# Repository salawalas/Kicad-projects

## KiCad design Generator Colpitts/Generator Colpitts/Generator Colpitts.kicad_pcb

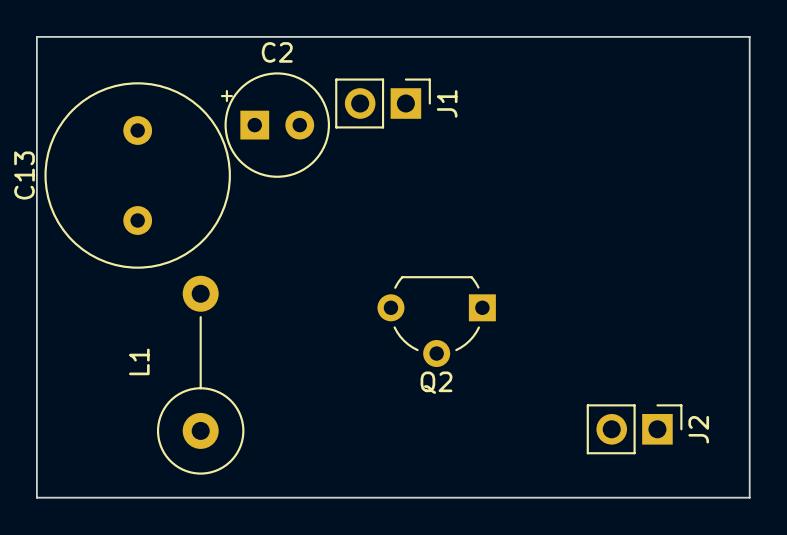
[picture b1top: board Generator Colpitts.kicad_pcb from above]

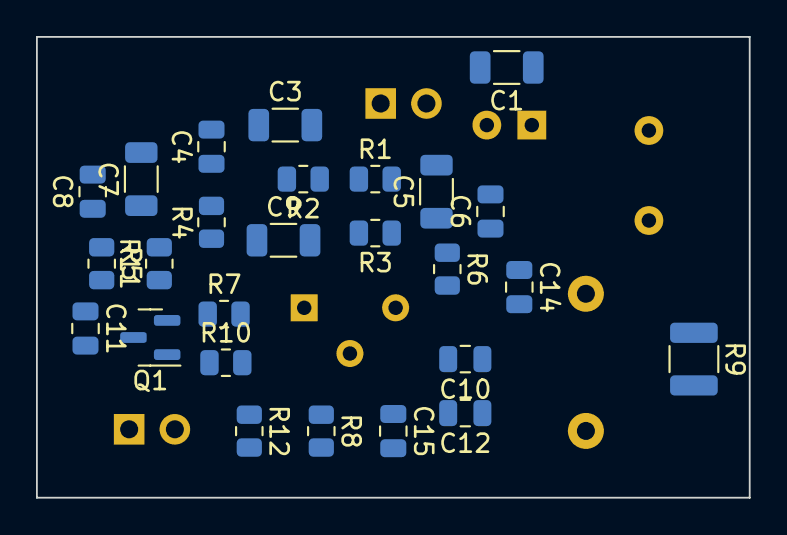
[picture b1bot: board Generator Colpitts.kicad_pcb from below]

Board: 2 copper layers, 39.6 x 25.6 mm, 32 parts (26 on the bottom side), 13 nets, no tracks yet.

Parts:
C1, C5: 100n; C_1206_3216Metric
C2: 47u/16V; CP_Radial_Tantal_D5.5mm_P2.50mm
C3, C7, C9: 47n; C_1206_3216Metric
C4, C6: 1n; C_0805_2012Metric
C8: 2n2; C_0805_2012Metric
C10: 5.6p; C_0805_2012Metric
C11: 47n; C_0805_2012Metric
C12: 24p; C_0805_2012Metric
C13: 3-12pF; C_Radial_D10.0mm_H12.5mm_P5.00mm
C14: 33p; C_0805_2012Metric
C15: 16p; C_0805_2012Metric
J1, J2: Conn_01x02_Female; PinHeader_1x02_P2.54mm_Vertical
L1: 48nH; L_Axial_L14.0mm_D4.5mm_P7.62mm_Vertical_Fastron_LACC
Q1: BFS17; SOT-23
Q2: BF240; TO-92L_Wide
R1: 100; R_0805_2012Metric
R2, R7: 51; R_0805_2012Metric
R3: 1k3; R_0805_2012Metric
R4: 4k7; R_0805_2012Metric
R5: 33; R_0805_2012Metric
R6: 8k2; R_0805_2012Metric
R8: 2k7; R_0805_2012Metric
R9: R_Small; R_1210_3225Metric
R10: 7k5; R_0805_2012Metric
R11: 300; R_0805_2012Metric
R12: 430; R_0805_2012Metric

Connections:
+12V: C1.1, C2.1, C5.1, C6.1, J1.1, R1.2, R2.1
GND: C1.2, C2.2, C3.2, C4.2, C5.2, C6.2, C7.2, C8.2, C13.2, C14.1, C15.2, J1.2, J2.2, L1.1, R8.2, R9.2, R10.1, R11.2, R12.2
unnamed: C3.1, C4.1, R1.1, R3.1, R6.1
unnamed: C7.1, C8.1, R2.2, R4.2, R5.1
unnamed: C9.1, R4.1, R7.2, R10.2
unnamed: C9.2, Q2.1 (C), R3.2
unnamed: C10.1, C13.1, C14.2, L1.2, R9.1
unnamed: C10.2, C12.1, Q2.3 (B), R6.2, R8.1
unnamed: C11.1, Q1.2 (E), R11.1
unnamed: C11.2, J2.1
unnamed: C12.2, C15.1, Q2.2 (E), R12.1
unnamed: Q1.1 (B), R7.1
unnamed: Q1.3 (C), R5.2

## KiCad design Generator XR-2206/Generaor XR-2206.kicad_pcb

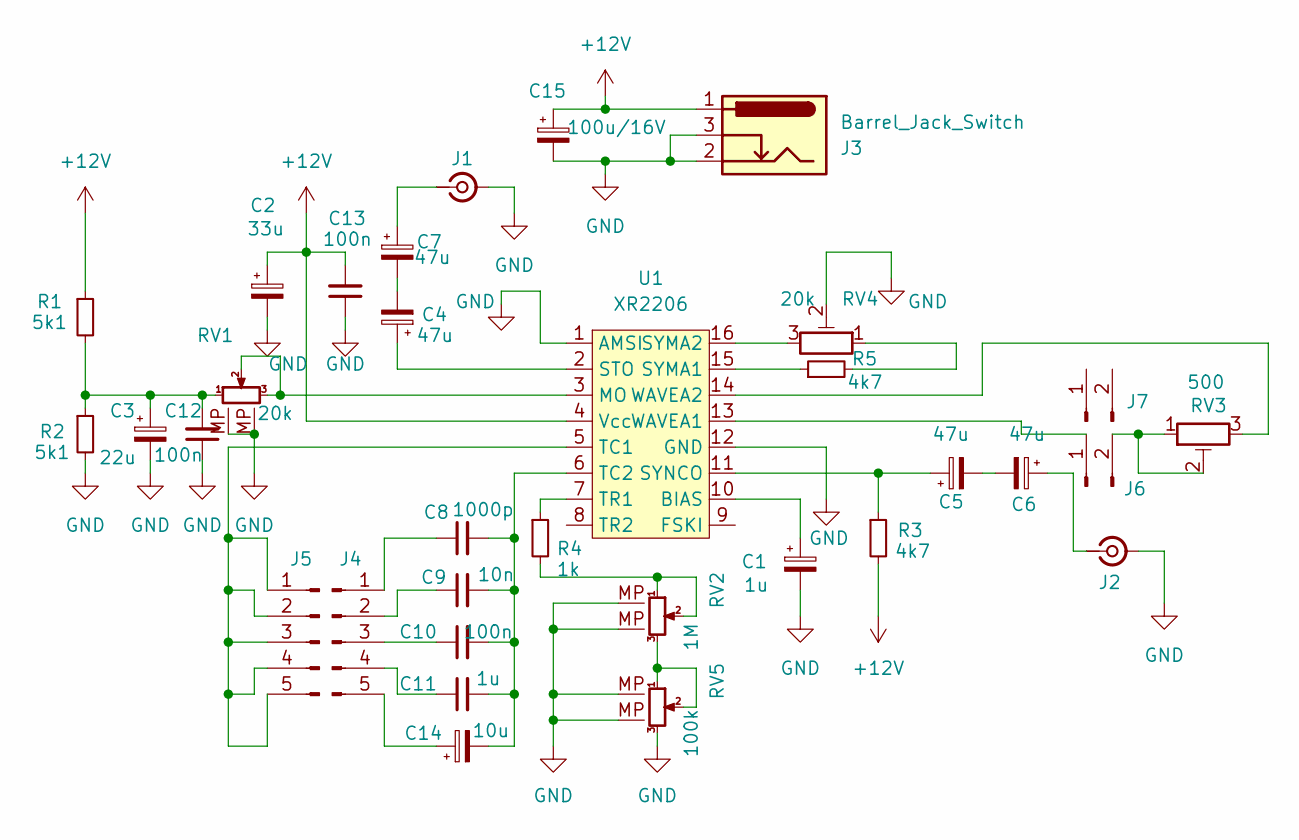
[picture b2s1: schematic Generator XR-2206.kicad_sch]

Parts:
C1: 1u; CP_Radial_Tantal_D5.5mm_P5.00mm
C2: 33u; CP_Radial_Tantal_D5.5mm_P5.00mm
C3: 22u; CP_Radial_Tantal_D5.5mm_P5.00mm
C4, C5, C6, C7: 47u; CP_Radial_D6.3mm_P2.50mm
C8: 1000p; C_Axial_L5.1mm_D3.1mm_P7.50mm_Horizontal
C9: 10n; C_Axial_L5.1mm_D3.1mm_P7.50mm_Horizontal
C10, C12, C13: 100n; C_Axial_L5.1mm_D3.1mm_P7.50mm_Horizontal
C11: 1u; C_Axial_L5.1mm_D3.1mm_P7.50mm_Horizontal
C14: 10u; CP_Radial_D6.3mm_P2.50mm
C15: 100u/16V; CP_Radial_D6.3mm_P2.50mm
J1, J2: Conn_Coaxial_Small; BNC_TEConnectivity_1478035_Horizontal
J3: Barrel_Jack_Switch; BarrelJack_GCT_DCJ200-10-A_Horizontal
J4, J5: Conn_01x05_Pin; PinHeader_1x05_P2.54mm_Vertical
J6, J7: Conn_01x02_Pin; PinHeader_1x02_P2.54mm_Vertical
R1, R2: 5k1; R_Axial_DIN0207_L6.3mm_D2.5mm_P10.16mm_Horizontal
R3, R5: 4k7; R_Axial_DIN0207_L6.3mm_D2.5mm_P10.16mm_Horizontal
R4: 1k; R_Axial_DIN0207_L6.3mm_D2.5mm_P10.16mm_Horizontal
RV1: 20k; Potentiometer_Alps_RK09K_Single_Vertical
RV2: 1M; Potentiometer_Alps_RK09K_Single_Vertical
RV3: 500; Potentiometer_Bourns_3296W_Vertical
RV4: 20k; Potentiometer_Bourns_3296W_Vertical
RV5: 100k; Potentiometer_Alps_RK09K_Single_Vertical
U1: XR2206; DIP-16_W7.62mm_Socket

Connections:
+12V: C2.1, C13.2, C15.1, J3.1, R1.1, R3.2, U1.4 (Vcc)
GND: C1.2, C2.2, C3.2, C12.1, C13.1, C15.2, J1.2 (Ext), J2.2 (Ext), J3.2, J3.3, R2.2, RV1.MP, RV2.MP, RV4.2, RV5.3, RV5.MP, U1.1 (AMSI), U1.12 (GND)
unnamed: C4.2, C7.2
unnamed: C5.2, C6.2
unnamed: C3.1, C12.2, R1.2, R2.1, RV1.1
unnamed: C7.1, J1.1 (In)
unnamed: C6.1, J2.1 (In)
unnamed: C8.1, J4.1
unnamed: C9.1, J4.2
unnamed: C10.1, J4.3
unnamed: C11.1, J4.4
unnamed: C14.1, J4.5
unnamed: J5.1, J5.2, J5.3, J5.4, J5.5, U1.5 (TC1)
unnamed: J6.1, U1.13 (WAVEA1)
unnamed: J6.2, RV3.1, RV3.2
unnamed: R4.2, RV2.1, RV2.2
unnamed: R5.2, RV4.1
unnamed: RV2.3, RV5.1, RV5.2
unnamed: C1.1, U1.10 (BIAS)
unnamed: RV1.2, RV1.3, U1.3 (MO)
unnamed: C4.1, U1.2 (STO)
unnamed: R5.1, U1.15 (SYMA1)
unnamed: RV4.3, U1.16 (SYMA2)
unnamed: C5.1, R3.1, U1.11 (SYNCO)
unnamed: C8.2, C9.2, C10.2, C11.2, C14.2, U1.6 (TC2)
unnamed: R4.1, U1.7 (TR1)
unnamed: RV3.3, U1.14 (WAVEA2)

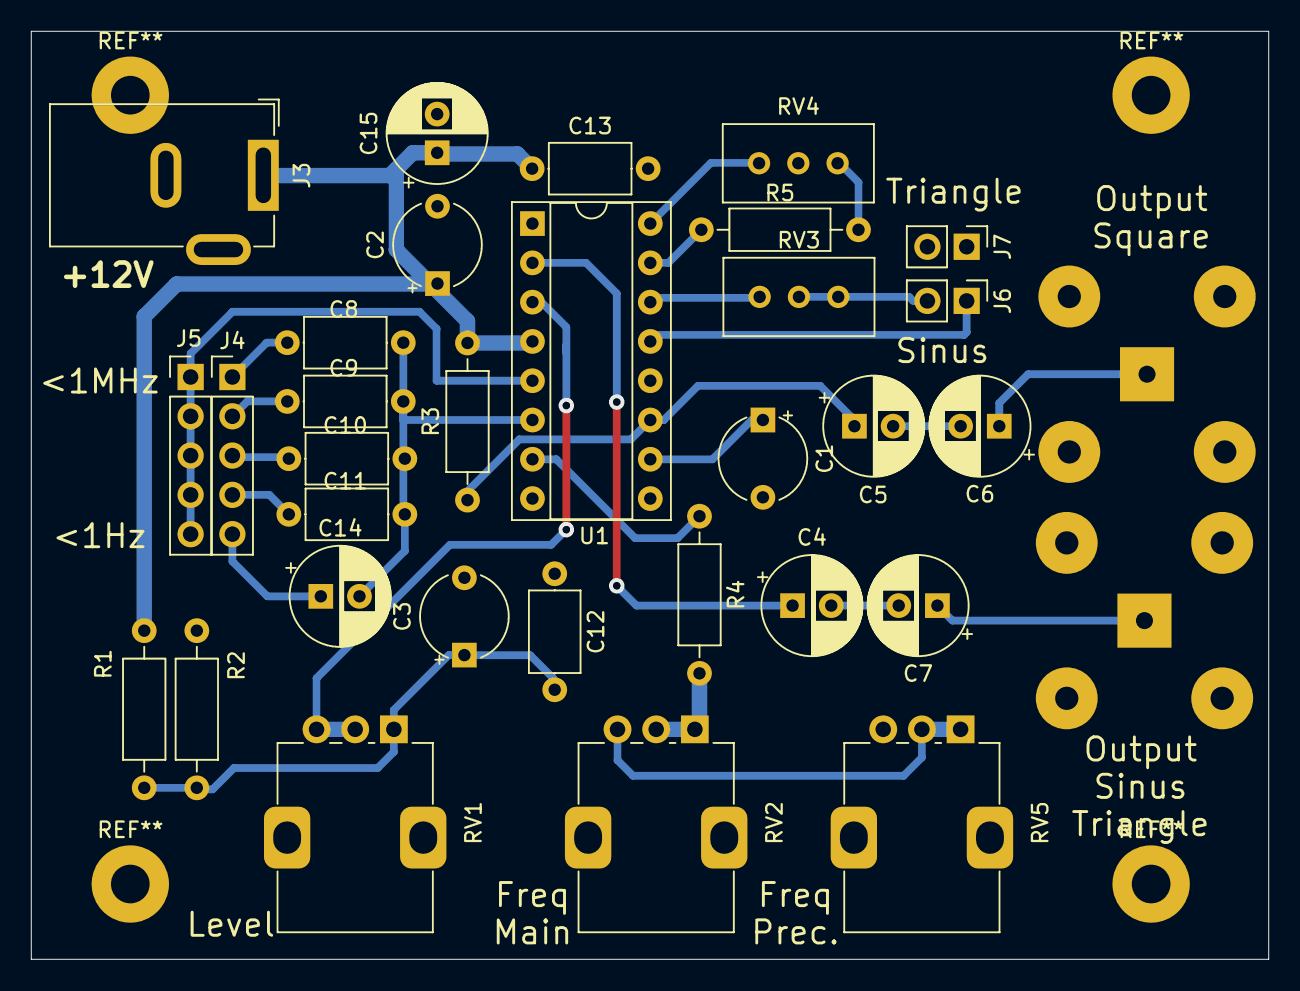
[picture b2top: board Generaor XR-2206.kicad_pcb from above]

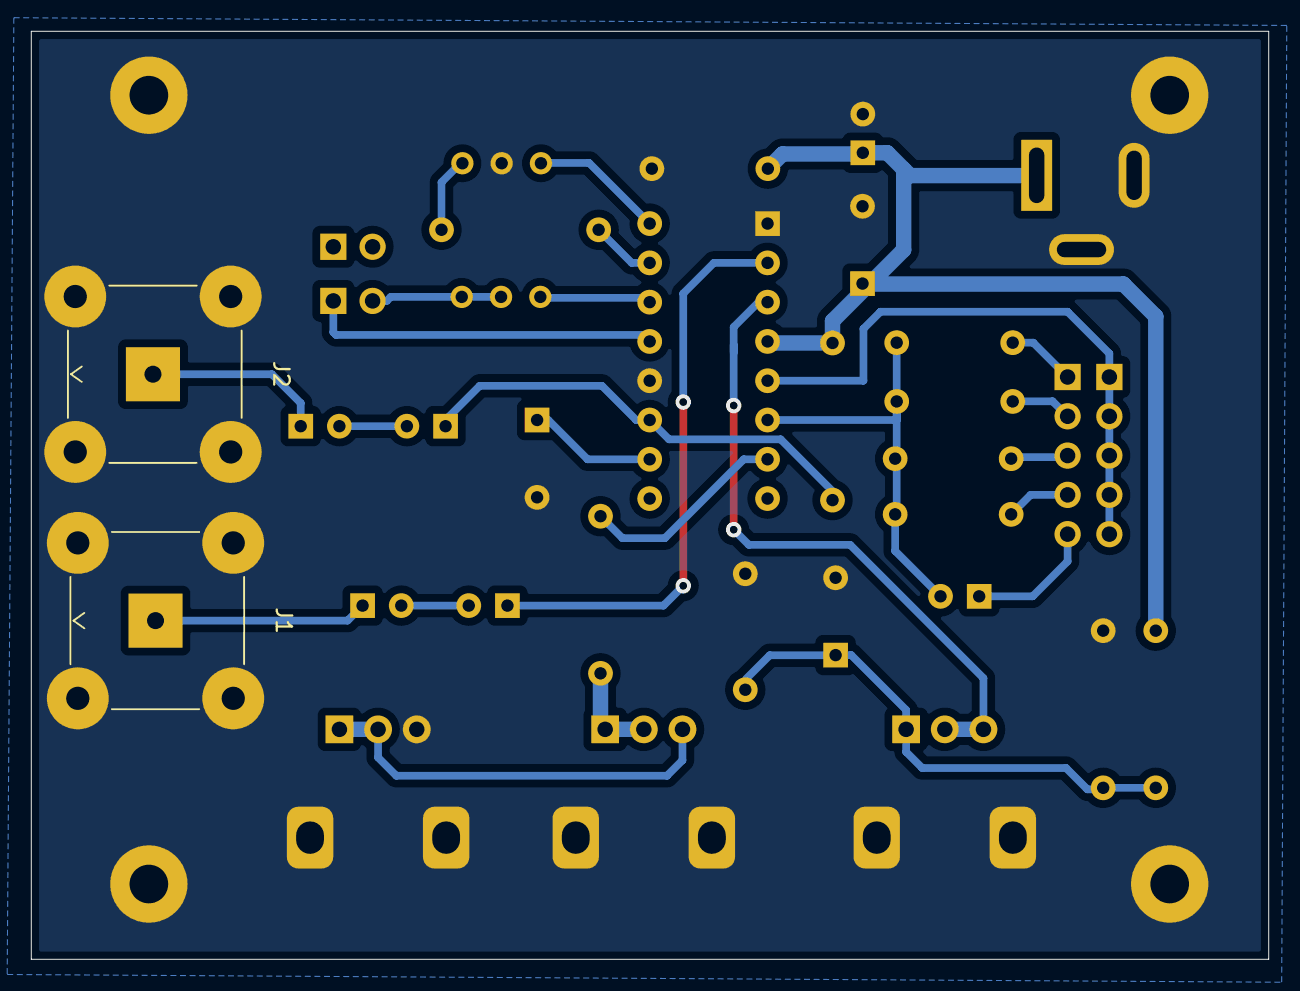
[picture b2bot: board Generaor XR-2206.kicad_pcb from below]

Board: 2 copper layers, 80.0 x 60.0 mm, 33 parts (2 on the bottom side), 27 nets.

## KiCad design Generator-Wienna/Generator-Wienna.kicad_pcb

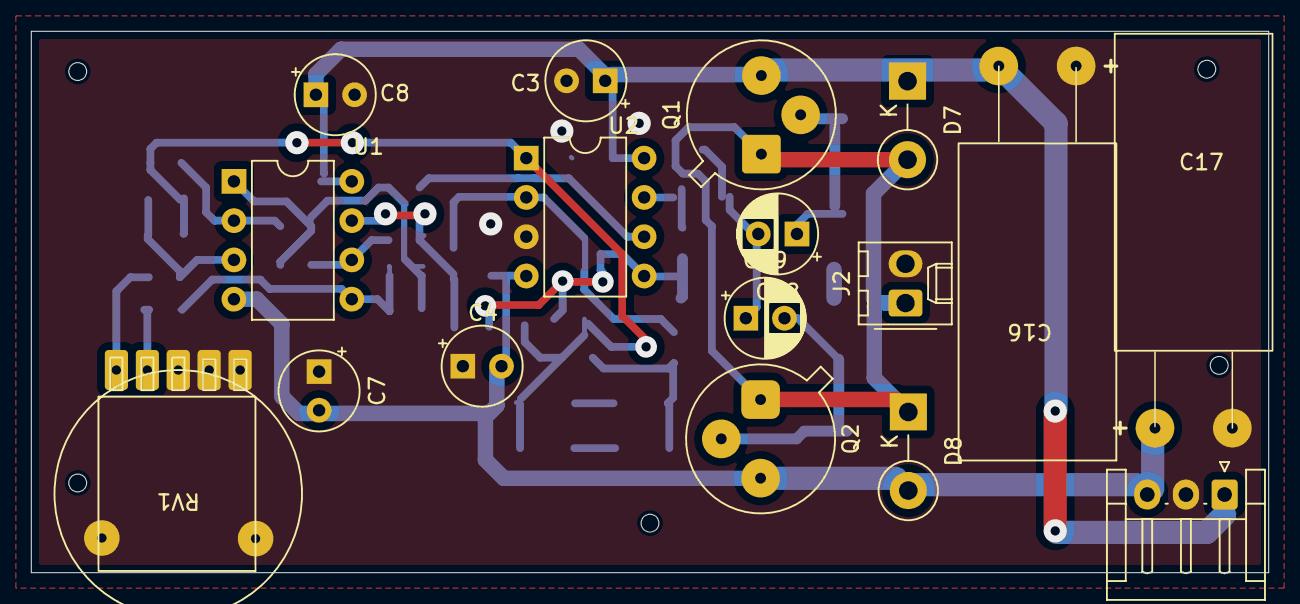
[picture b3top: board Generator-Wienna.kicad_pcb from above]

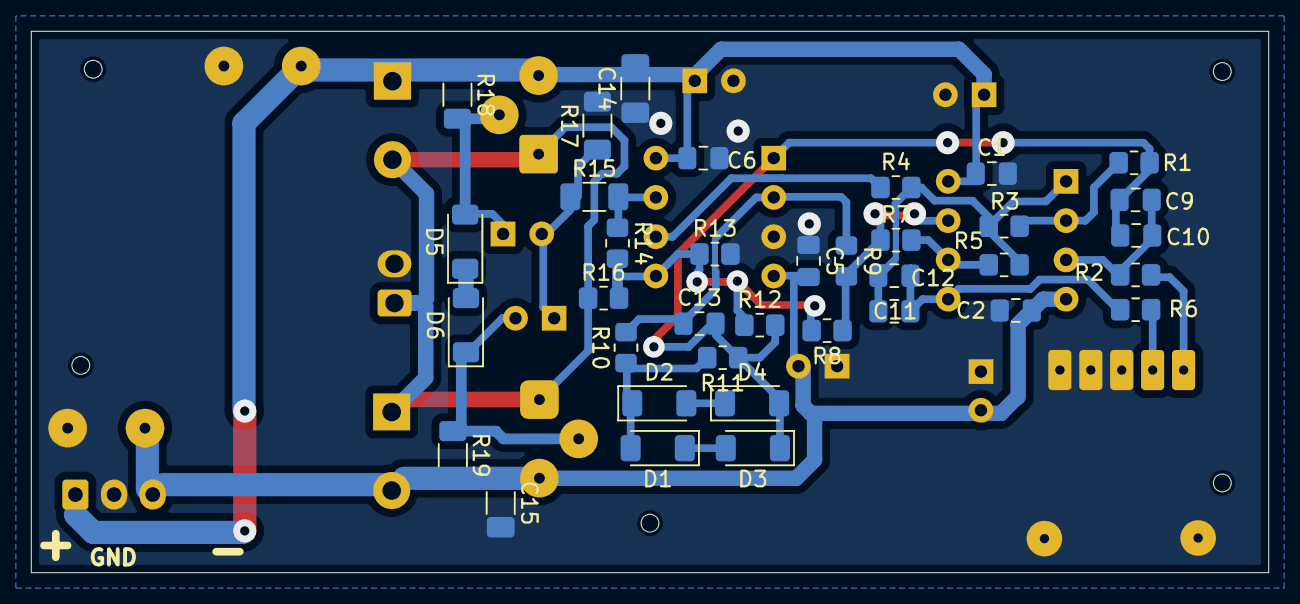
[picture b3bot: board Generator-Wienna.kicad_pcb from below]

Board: 2 copper layers, 80.0 x 35.0 mm, 53 parts (36 on the bottom side), 24 nets.

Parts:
C1, C2, C5, C6: 100n; C_0805_2012Metric_Pad1.18x1.45mm_HandSolder
C3, C4, C7, C8: 22u/10v; CP_Radial_Tantal_D5.0mm_P2.50mm
C9, C10, C11, C12: 220n; C_0805_2012Metric_Pad1.18x1.45mm_HandSolder
C13: 270p; C_0805_2012Metric_Pad1.18x1.45mm_HandSolder
C14, C15: 100n; C_1206_3216Metric_Pad1.33x1.80mm_HandSolder
C16: 2200u/6.3v; 2200u_6.3V
C17: 2200u/6.3V; 2200u_6.3V
C18, C19: 100u/16V; CP_Radial_D5.0mm_P2.50mm
D1, D2, D3, D4, D5, D6: 1N4148W; D_MiniMELF
D7, D8: 1N4001; D_DO-15_P5.08mm_Vertical_KathodeUp
J1: Power; JST_EH_S3B-EH_1x03_P2.50mm_Horizontal
J2: Output; Molex_KK-254_AE-6410-02A_1x02_P2.54mm_Vertical
Q1: BC141; TO-39-3
Q2: BC161; TO-39-3
R1, R3, R4, R5, R7, R8, R12, R14: 10k; R_0805_2012Metric_Pad1.20x1.40mm_HandSolder
R2, R6: 43k; R_0805_2012Metric_Pad1.20x1.40mm_HandSolder
R9: 4k7; R_0805_2012Metric_Pad1.20x1.40mm_HandSolder
R10: 1k8; R_0805_2012Metric_Pad1.20x1.40mm_HandSolder
R11: 3k9; R_0805_2012Metric_Pad1.20x1.40mm_HandSolder
R13: 15k; R_0805_2012Metric_Pad1.20x1.40mm_HandSolder
R15: 100; R_1206_3216Metric_Pad1.30x1.75mm_HandSolder
R16: 100k; R_0805_2012Metric_Pad1.20x1.40mm_HandSolder
R17: 5k1; R_1206_3216Metric_Pad1.30x1.75mm_HandSolder
R18, R19: 2k; R_1206_3216Metric_Pad1.30x1.75mm_HandSolder
RV1: Potencjometr_podwójny_mp3
U1, U2: RC4558; DIP-8_W7.62mm

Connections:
+5V: C1.1, C3.1, C6.1, C8.1, C14.2, C16.1, D7.1 (K), J1.1, Q1.3 (C), R18.1, U1.8 (V+), U2.8 (V+)
-5V: C2.1, C4.2, C5.2, C7.2, C15.1, C17.2, D8.2 (A), J1.3, Q2.3 (C), R19.2, U1.4 (V-), U2.4 (V-)
GND: C1.2, C2.2, C3.2, C4.1, C5.1, C6.2, C7.1, C8.2, C14.1, C15.2, C16.2, C17.1, J1.2, J2.2, R13.2, R17.2, RV1.1 (GND), RV1.2 (L_slider), RV1.3 (R_slider), RV1.6 (GND), RV1.7 (GND), U2.3 (+)
unnamed: C11.1, C12.1, R3.2, R4.2, R5.2, U1.1
unnamed: C18.2, C19.1, R15.1, R17.1
unnamed: D1.2 (A), D2.1 (K), R10.1, R11.2
unnamed: D1.1 (K), D3.2 (A)
unnamed: D2.2 (A), D4.1 (K)
unnamed: C9.1, C10.1, C13.2, D3.1 (K), D4.2 (A), R1.1, R11.1, R12.2, U2.1
unnamed: C18.1, D5.2 (A), Q1.2 (B), R18.2
unnamed: D5.1 (K), D6.2 (A)
unnamed: C19.2, D6.1 (K), Q2.2 (B), R19.1
unnamed: D7.2 (A), D8.1 (K), J2.1, Q1.1 (E), Q2.1 (E), R16.1
unnamed: R7.1, R8.1, R9.2, U1.7
unnamed: R14.1, R15.2, U2.7
unnamed: R2.1, RV1.5 (L_out)
unnamed: R6.1, RV1.4 (R_out)
unnamed: C9.2, C10.2, R2.2, U1.3 (+)
unnamed: R1.2, R3.1, U1.2 (-)
unnamed: C11.2, C12.2, R6.2, U1.5 (+)
unnamed: R5.1, R7.2, U1.6 (-)
unnamed: C13.1, R9.1, R10.2, U2.2 (-)
unnamed: R8.2, R12.1, R13.1, R14.2, R16.2, U2.5 (+)
unnamed: R4.1, U2.6 (-)

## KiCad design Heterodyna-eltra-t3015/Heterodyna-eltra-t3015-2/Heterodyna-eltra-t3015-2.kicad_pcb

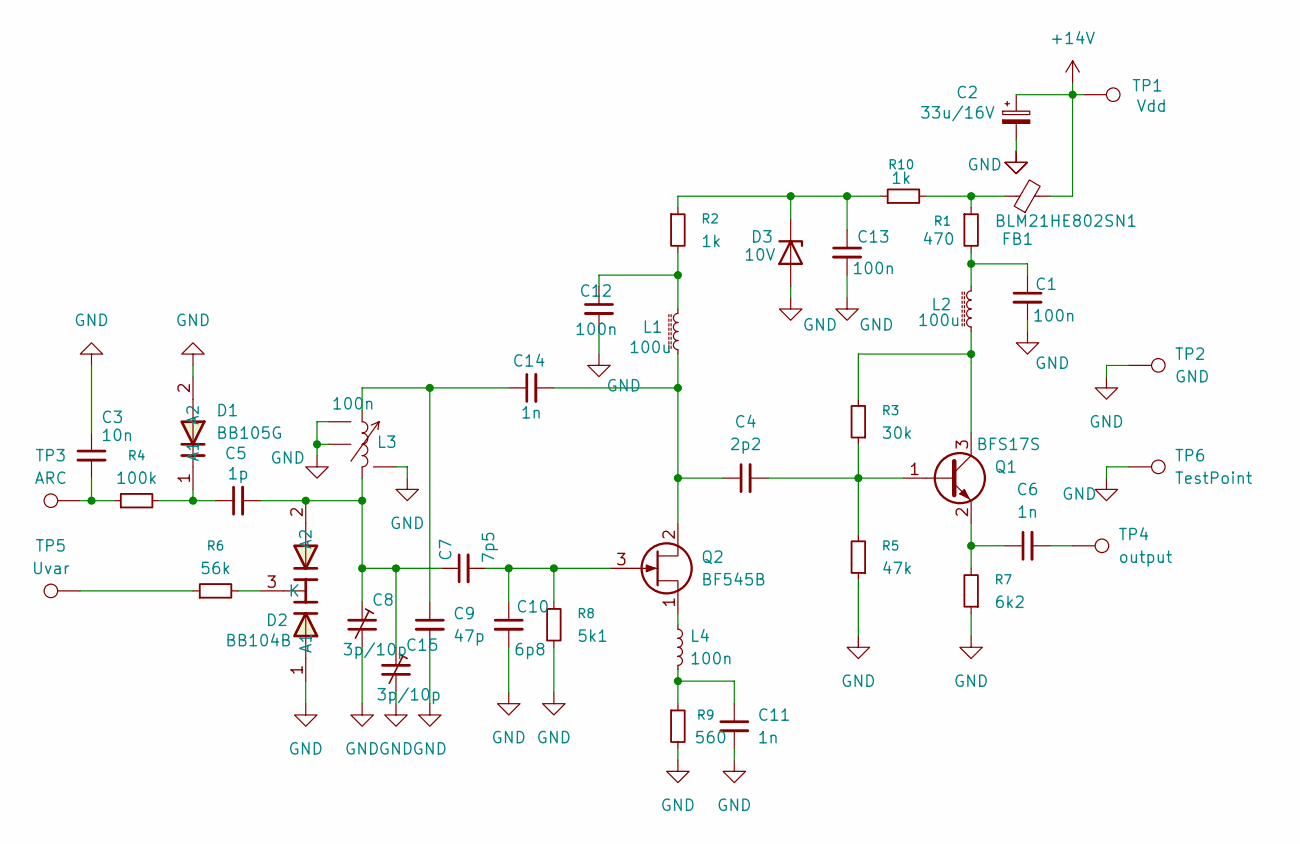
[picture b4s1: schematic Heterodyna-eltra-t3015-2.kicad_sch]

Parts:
C1, C12, C13: 100n; C_0805_2012Metric
C2: 33u/16V; CP_Radial_Tantal_D6.0mm_P2.50mm
C3: 10n; C_0805_2012Metric
C4: 2p2; C_0805_2012Metric
C5: 1p; C_0805_2012Metric
C6, C11, C14: 1n; C_0805_2012Metric
C7: 7p5; C_0805_2012Metric
C8: 3p/10p; Trymer 3-10pF
C9: 47p; C_0805_2012Metric
C10: 6p8; C_0805_2012Metric
C15: 3p/10p; Trymer 10pF
D1: BB105G
D2: BB104B
D3: 10V; D_DO-35_SOD27_P3.81mm_Vertical_AnodeUp
FB1: BLM21HE802SN1; L_0805_2012Metric
L1, L2: 100u; L_1206_3216Metric
L3: 100n; Cewka-powietrzna-5mm
L4: 100n; L_0805_2012Metric
Q1: BFS17S; TSOT-23
Q2: BF545B; SOT-23
R1: 470; R_1206_3216Metric
R2, R10: 1k; R_0805_2012Metric
R3: 30k; R_0805_2012Metric
R4: 100k; R_0805_2012Metric
R5: 47k; R_0805_2012Metric
R6: 56k; R_0805_2012Metric
R7: 6k2; R_0805_2012Metric
R8: 5k1; R_0805_2012Metric
R9: 560; R_0805_2012Metric
TP1: Vdd; SolderWire-0.1sqmm_1x01_D0.4mm_OD1mm
TP2: GND; SolderWire-0.1sqmm_1x01_D0.4mm_OD1mm
TP3: ARC; SolderWire-0.1sqmm_1x01_D0.4mm_OD1mm
TP4: output; SolderWire-0.1sqmm_1x01_D0.4mm_OD1mm
TP5: Uvar; SolderWire-0.1sqmm_1x01_D0.4mm_OD1mm
TP6: TestPoint; Pin_D0.7mm_L6.5mm_W1.8mm_FlatFork

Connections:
+14V: C2.1, FB1.2, TP1.1
GND: C1.2, C2.2, C3.1, C8.2, C9.2, C10.2, C11.2, C12.2, C13.2, C15.2, D1.2 (A2), D2.1 (A1), D3.2 (A), L3.4 (base), L3.5 (base), L3.6 (base), R5.1, R7.1, R8.2, R9.2, TP2.1, TP6.1
unnamed: C1.1, L2.2, R1.2
unnamed: C3.2, R4.1, TP3.1
unnamed: C6.2, TP4.1
unnamed: C11.1, L4.2, R9.1
unnamed: C12.1, L1.2, R2.2
unnamed: C9.1, C14.1, L3.1
unnamed: C5.1, D1.1 (A1), R4.2
unnamed: C5.2, C7.1, C8.1, C15.1, D2.2 (A2), L3.2
unnamed: D2.3 (K), R6.2
unnamed: C13.1, D3.1 (K), R2.1, R10.1
unnamed: FB1.1, R1.1, R10.2
unnamed: C4.2, Q1.1 (B), R3.1, R5.2
unnamed: L2.1, Q1.3 (C), R3.2
unnamed: C6.1, Q1.2 (E), R7.2
unnamed: C4.1, C14.2, L1.1, Q2.2 (D)
unnamed: C7.2, C10.1, Q2.3 (G), R8.1
unnamed: L4.1, Q2.1 (S)
unnamed: R6.1, TP5.1

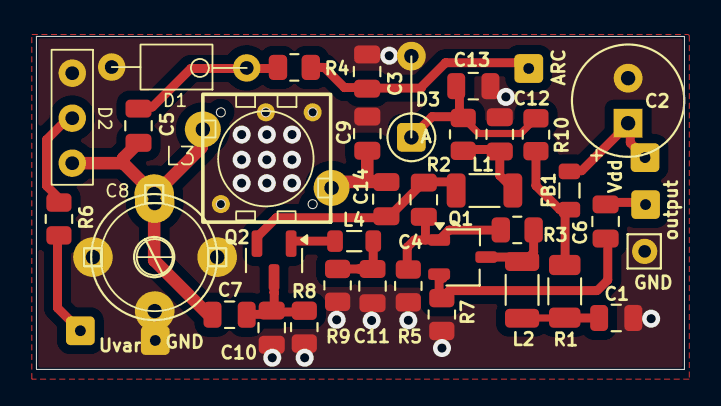
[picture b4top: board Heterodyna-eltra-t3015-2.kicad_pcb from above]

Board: 4 copper layers, 36.0 x 18.5 mm, 41 parts (0 on the bottom side), 20 nets.

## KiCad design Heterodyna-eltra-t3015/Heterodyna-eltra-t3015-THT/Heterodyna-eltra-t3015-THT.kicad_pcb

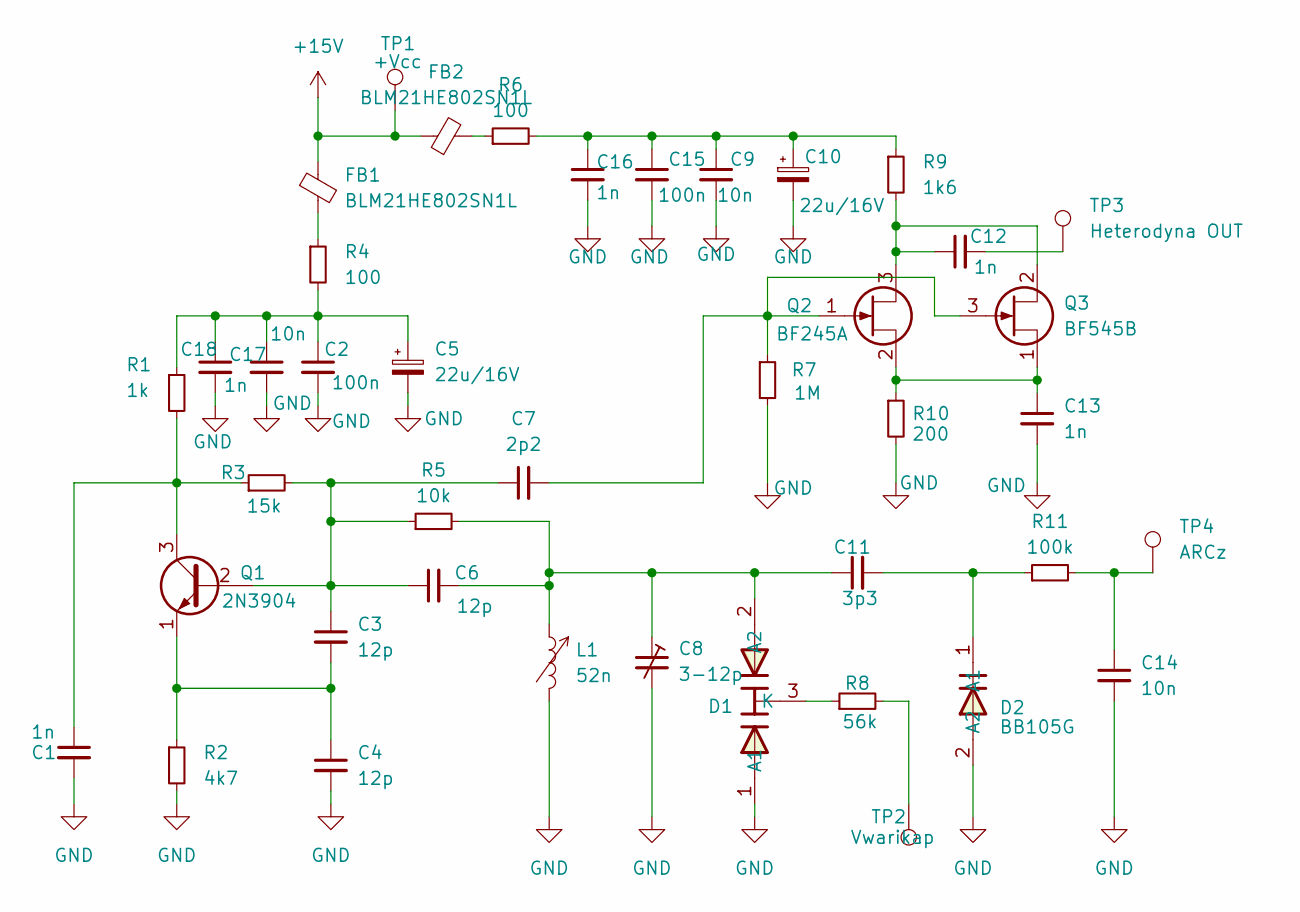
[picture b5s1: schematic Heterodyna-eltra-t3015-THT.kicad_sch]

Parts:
C1, C12, C13: 1n; C_Disc_D4.3mm_W1.9mm_P5.00mm
C2, C9: 100n; C_Disc_D4.7mm_W2.5mm_P5.00mm
C3, C4, C6: 12p; C_Disc_D4.3mm_W1.9mm_P5.00mm
C5, C10: 22u/16V; CP_Radial_Tantal_D5.0mm_P2.50mm
C7: 2p2; C_Disc_D4.3mm_W1.9mm_P5.00mm
C8: 3-12p; Trymer 3-10pF
C11: 3p3; C_Disc_D4.3mm_W1.9mm_P5.00mm
C14: 10n; C_Disc_D4.3mm_W1.9mm_P5.00mm
C15, C17: 10n; C_Disc_D4.7mm_W2.5mm_P5.00mm
C16, C18: 1n; C_Disc_D4.7mm_W2.5mm_P5.00mm
D1: BB104B
D2: BB105G
FB1, FB2: BLM21HE802SN1L; R_Axial_DIN0204_L3.6mm_D1.6mm_P7.62mm_Horizontal
L1: 52n; Cewka-powietrzna-5mm
Q1: 2N3904; TO-92_Wide
Q2: BF245A; TO-92_Wide
Q3: BF545B; SOT-23
R1: 1k; R_Axial_DIN0204_L3.6mm_D1.6mm_P7.62mm_Horizontal
R2: 4k7; R_Axial_DIN0204_L3.6mm_D1.6mm_P7.62mm_Horizontal
R3: 15k; R_Axial_DIN0204_L3.6mm_D1.6mm_P7.62mm_Horizontal
R4, R6: 100; R_Axial_DIN0204_L3.6mm_D1.6mm_P7.62mm_Horizontal
R5: 10k; R_Axial_DIN0204_L3.6mm_D1.6mm_P7.62mm_Horizontal
R7: 1M; R_Axial_DIN0204_L3.6mm_D1.6mm_P7.62mm_Horizontal
R8: 56k; R_Axial_DIN0204_L3.6mm_D1.6mm_P7.62mm_Horizontal
R9: 1k6; R_Axial_DIN0204_L3.6mm_D1.6mm_P7.62mm_Horizontal
R10: 200; R_Axial_DIN0204_L3.6mm_D1.6mm_P7.62mm_Horizontal
R11: 100k; R_Axial_DIN0204_L3.6mm_D1.6mm_P7.62mm_Horizontal
TP1: +Vcc; PinHeader_1x01_P1.00mm_Vertical
TP2: Vwarikap; PinHeader_1x01_P1.00mm_Vertical
TP3: Heterodyna OUT; PinHeader_1x01_P1.00mm_Vertical
TP4: ARCz; PinHeader_1x01_P1.00mm_Vertical

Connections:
+15V: FB1.2, FB2.1, TP1.1
GND: C1.2, C2.2, C4.2, C5.2, C8.2, C9.2, C10.2, C13.2, C14.2, C15.2, C16.2, C17.2, C18.2, D1.1 (A1), D2.2 (A2), L1.2, L1.4, L1.5, L1.6, L1.7, R2.2, R7.2, R10.2
unnamed: C9.1, C10.1, C15.1, C16.1, R6.2, R9.1
unnamed: C12.2, TP3.1
unnamed: C14.1, R11.2, TP4.1
unnamed: C2.1, C5.1, C17.1, C18.1, R1.1, R4.2
unnamed: C6.2, C8.1, C11.1, D1.2 (A2), L1.1, L1.3, R5.2
unnamed: D1.3 (K), R8.1
unnamed: C11.2, D2.1 (A1), R11.1
unnamed: FB1.1, R4.1
unnamed: FB2.2, R6.1
unnamed: C3.1, C6.1, C7.1, Q1.2 (B), R3.2, R5.1
unnamed: C1.1, Q1.3 (C), R1.2, R3.1
unnamed: C3.2, C4.1, Q1.1 (E), R2.1
unnamed: C12.1, Q2.3 (D), Q3.2 (D), R9.2
unnamed: C7.2, Q2.1 (G), Q3.3 (G), R7.1
unnamed: C13.1, Q2.2 (S), Q3.1 (S), R10.1
unnamed: R8.2, TP2.1

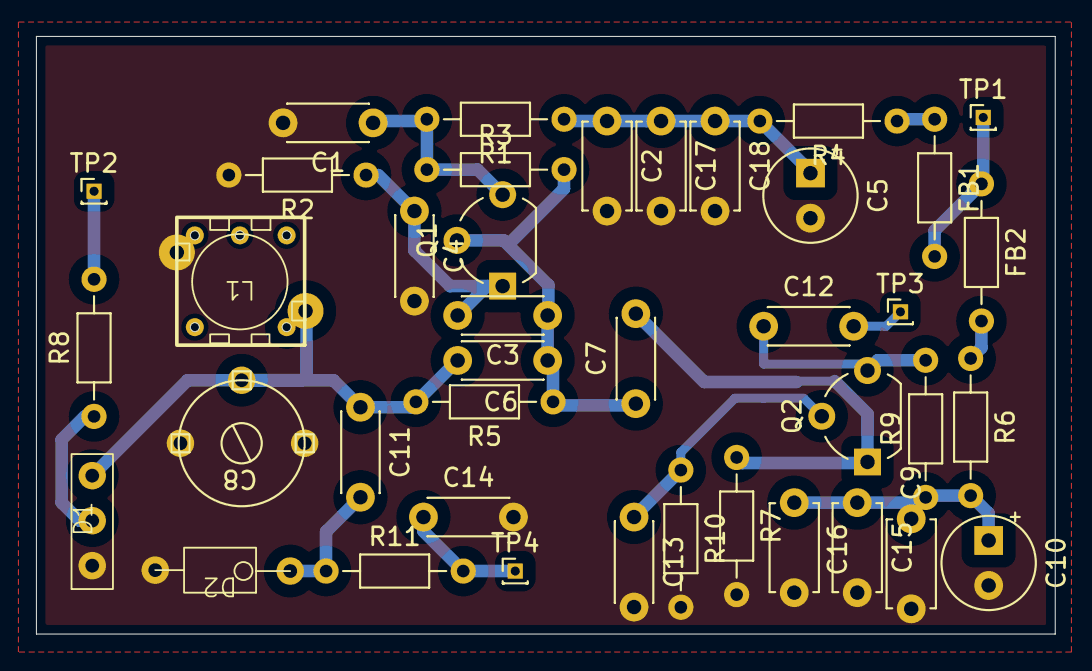
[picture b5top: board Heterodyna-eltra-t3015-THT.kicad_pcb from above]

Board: 2 copper layers, 56.6 x 33.2 mm, 41 parts (1 on the bottom side), 18 nets.

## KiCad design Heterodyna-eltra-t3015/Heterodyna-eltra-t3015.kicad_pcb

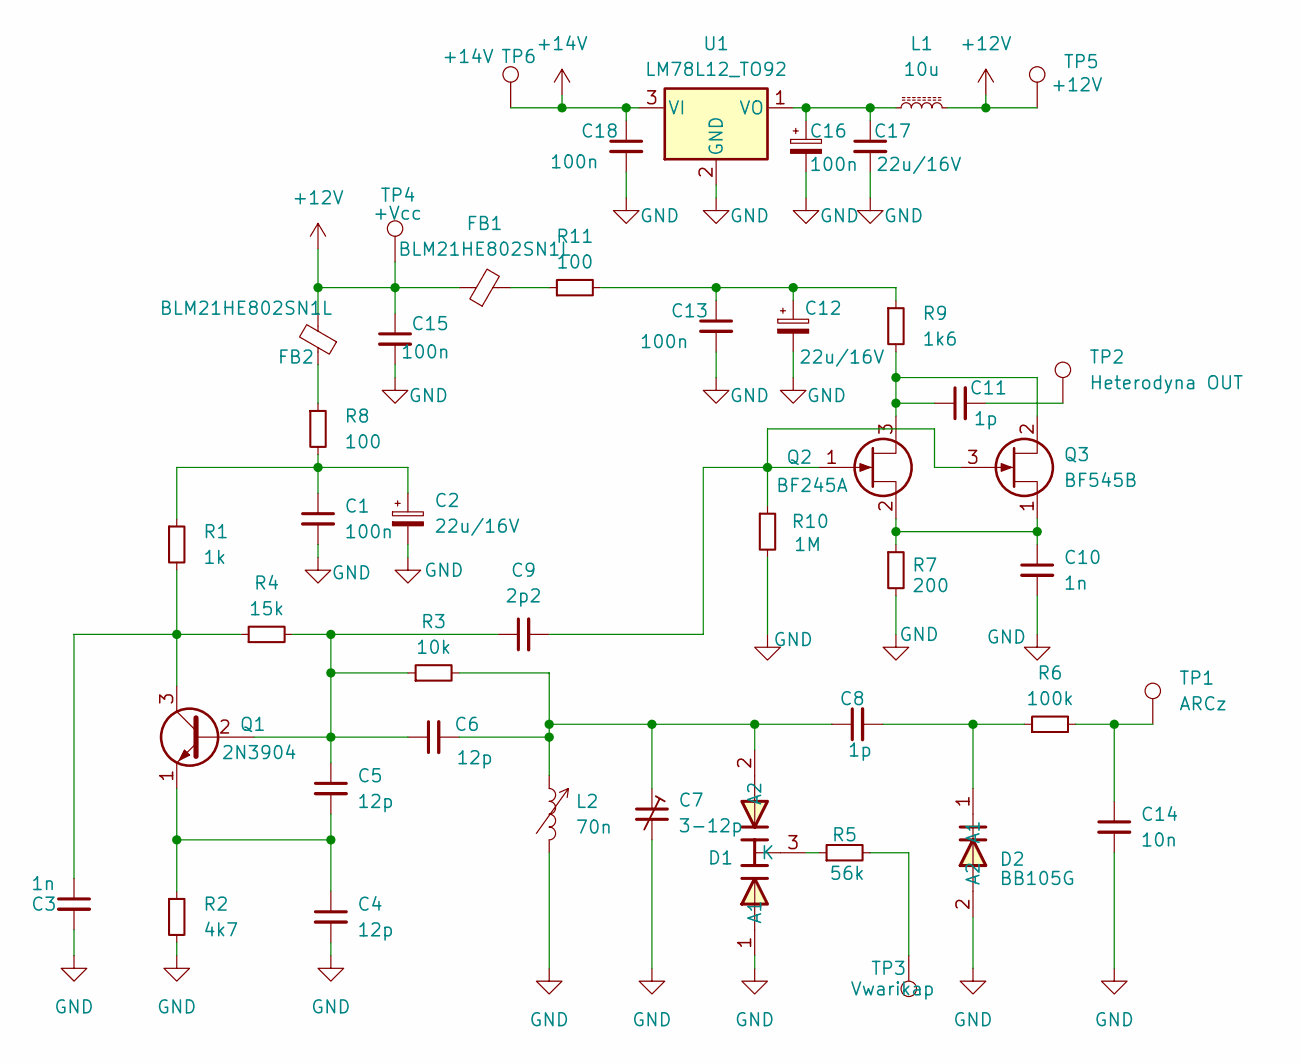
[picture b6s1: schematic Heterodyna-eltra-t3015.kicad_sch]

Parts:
C1, C13, C15, C17, C18: 100n; C_0805_2012Metric
C2, C12, C16: 22u/16V; CP_Radial_Tantal_D5.0mm_P2.50mm
C3, C10: 1n; C_0805_2012Metric
C4, C5, C6: 12p; C_0805_2012Metric
C7: 3-12p; Trymer 3-10pF
C8, C11: 1p; C_0805_2012Metric
C9: 2p2; C_0805_2012Metric
C14: 10n; C_0805_2012Metric
D1: BB104B
D2: BB105G
FB1, FB2: BLM21HE802SN1L; L_0805_2012Metric_Pad1.15x1.40mm_HandSolder
L1: 10u; L_Radial_D9.5mm_P5.00mm_Fastron_07HVP
L2: 70n; Cewka-powietrzna-5mm
Q1: 2N3904; TO-92_Inline
Q2: BF245A; TO-92_Inline
Q3: BF545B; SOT-23
R1: 1k; R_0805_2012Metric_Pad1.20x1.40mm_HandSolder
R2: 4k7; R_0805_2012Metric_Pad1.20x1.40mm_HandSolder
R3: 10k; R_0805_2012Metric_Pad1.20x1.40mm_HandSolder
R4: 15k; R_0805_2012Metric_Pad1.20x1.40mm_HandSolder
R5: 56k; R_0805_2012Metric_Pad1.20x1.40mm_HandSolder
R6: 100k; R_0805_2012Metric_Pad1.20x1.40mm_HandSolder
R7: 200; R_0805_2012Metric_Pad1.20x1.40mm_HandSolder
R8, R11: 100; R_0805_2012Metric_Pad1.20x1.40mm_HandSolder
R9: 1k6; R_0805_2012Metric_Pad1.20x1.40mm_HandSolder
R10: 1M; R_0805_2012Metric_Pad1.20x1.40mm_HandSolder
TP1: ARCz; PinHeader_1x01_P1.00mm_Vertical
TP2: Heterodyna OUT; PinHeader_1x01_P1.00mm_Vertical
TP3: Vwarikap; PinHeader_1x01_P1.00mm_Vertical
TP4: +Vcc; PinHeader_1x01_P1.00mm_Vertical
TP5: +12V; PinHeader_1x01_P1.00mm_Vertical
TP6: +14V; PinHeader_1x01_P1.00mm_Vertical
U1: LM78L12_TO92; TO-92L_HandSolder

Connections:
+12V: C15.1, FB1.1, FB2.2, L1.2, TP4.1, TP5.1
+14V: C18.1, TP6.1, U1.3 (VI)
GND: C1.2, C2.2, C3.2, C4.2, C7.2, C10.2, C12.2, C13.2, C14.2, C15.2, C16.2, C17.2, C18.2, D1.1 (A1), D2.2 (A2), L2.2, L2.4, L2.5, L2.6, L2.7, R2.2, R7.2, R10.2, U1.2 (GND)
unnamed: C1.1, C2.1, R1.1, R8.2
unnamed: C11.2, TP2.1
unnamed: C12.1, C13.1, R9.1, R11.2
unnamed: C14.1, R6.2, TP1.1
unnamed: C6.2, C7.1, C8.1, D1.2 (A2), L2.1, R3.2
unnamed: D1.3 (K), R5.1
unnamed: C8.2, D2.1 (A1), R6.1
unnamed: FB1.2, R11.1
unnamed: FB2.1, R8.1
unnamed: C5.1, C6.1, C9.1, Q1.2 (B), R3.1, R4.2
unnamed: C3.1, Q1.3 (C), R1.2, R4.1
unnamed: C4.1, C5.2, Q1.1 (E), R2.1
unnamed: C11.1, Q2.3 (D), Q3.2 (D), R9.2
unnamed: C9.2, Q2.1 (G), Q3.3 (G), R10.1
unnamed: C10.1, Q2.2 (S), Q3.1 (S), R7.1
unnamed: R5.2, TP3.1
unnamed: C16.1, C17.1, L1.1, U1.1 (VO)

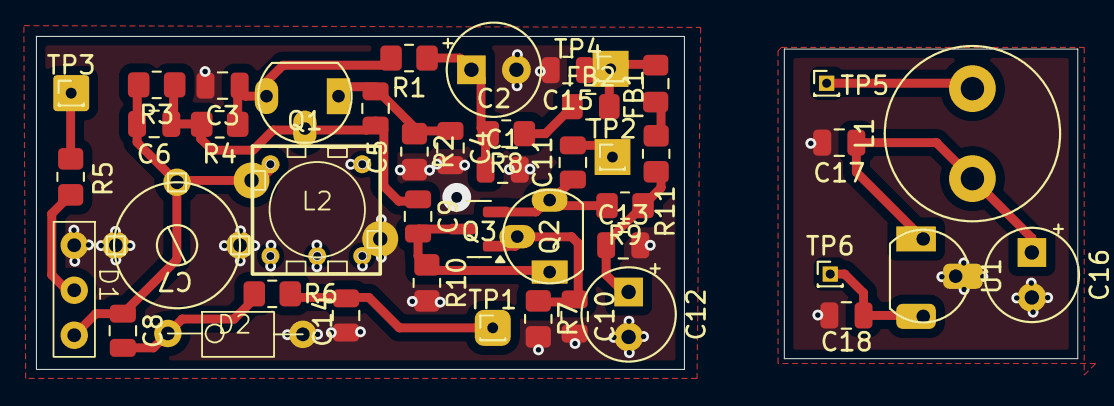
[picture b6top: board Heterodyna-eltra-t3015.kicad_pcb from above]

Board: 2 copper layers, 36.0 x 18.5 mm, 45 parts (0 on the bottom side), 20 nets.

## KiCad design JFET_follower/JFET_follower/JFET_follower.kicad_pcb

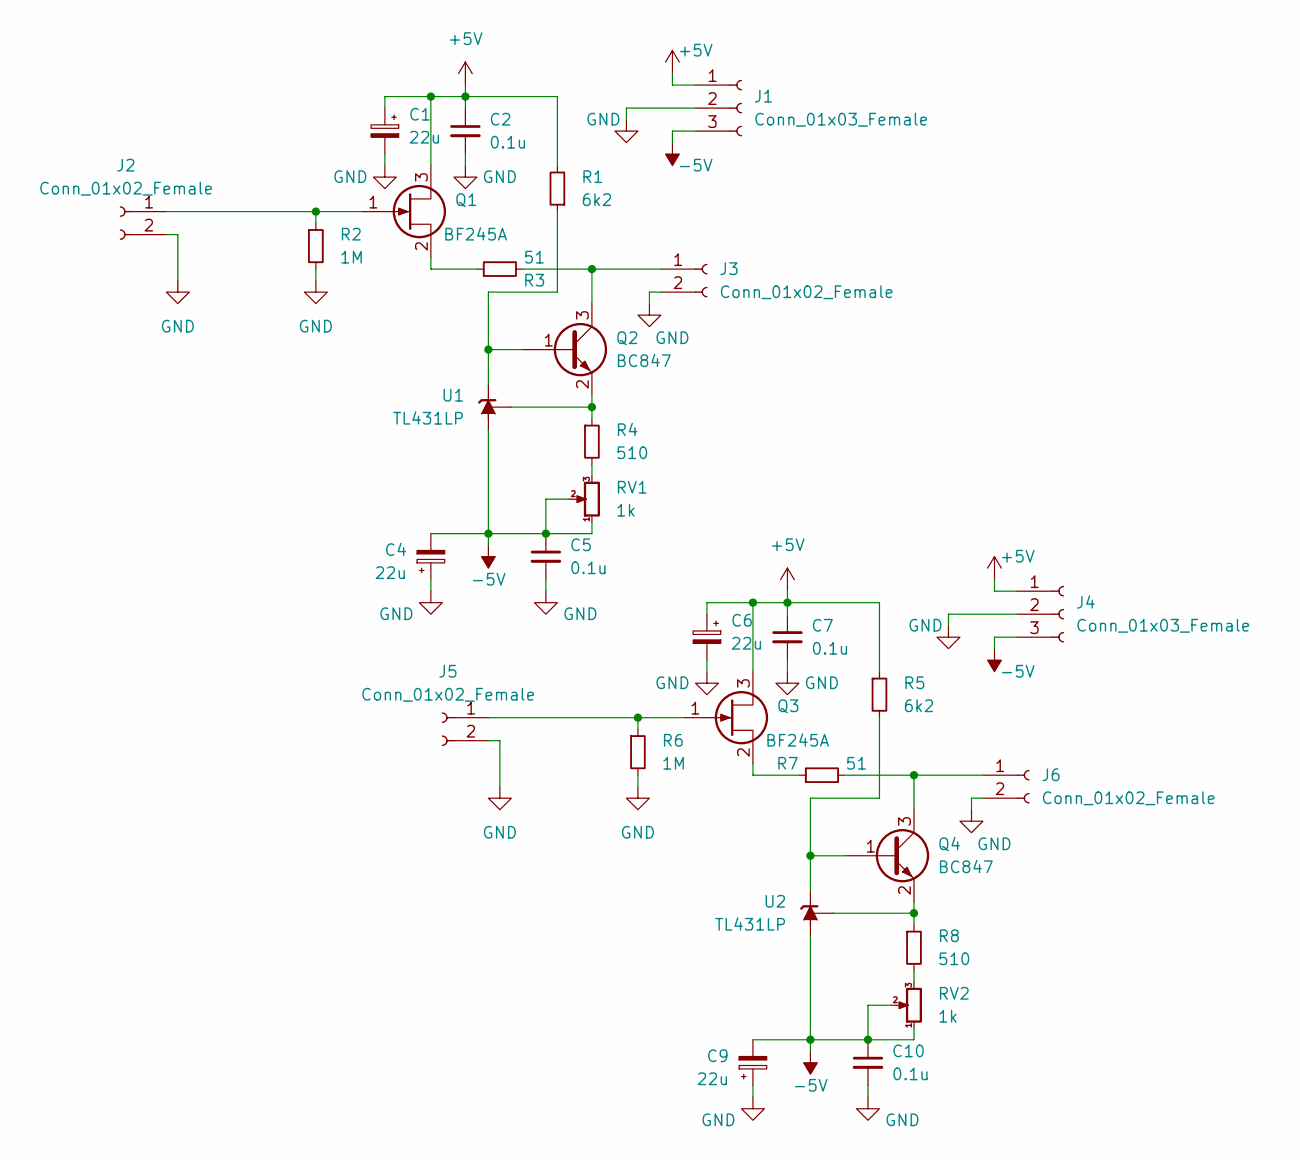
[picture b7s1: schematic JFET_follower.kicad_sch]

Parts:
C1, C4, C6, C9: 22u; CP_Radial_D5.0mm_P2.50mm
C2, C5, C7, C10: 0.1u; C_0805_2012Metric
J1, J4: Conn_01x03_Female; PinHeader_1x03_P2.54mm_Vertical
J2, J3, J5, J6: Conn_01x02_Female; PinHeader_1x02_P2.54mm_Vertical
Q1, Q3: BF245A; TO-92_Wide
Q2, Q4: BC847; SOT-23
R1, R5: 6k2; R_1206_3216Metric
R2, R6: 1M; R_1206_3216Metric
R3, R7: 51; R_1206_3216Metric
R4, R8: 510; R_1206_3216Metric
RV1, RV2: 1k; Potentiometer_Bourns_3314S_Horizontal
U1, U2: TL431LP; TO-92_Wide

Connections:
+5V: C1.1, C2.1, C6.1, C7.1, J1.1, J4.1, Q1.3 (D), Q3.3 (D), R1.2, R5.1
-5V: C4.2, C5.1, C9.2, C10.1, J1.3, J4.3, RV1.1, RV1.2, RV2.1, RV2.2, U1.2 (A), U2.2 (A)
GND: C1.2, C2.2, C4.1, C5.2, C6.2, C7.2, C9.1, C10.2, J1.2, J2.2, J3.2, J4.2, J5.2, J6.2, R2.2, R6.2
unnamed: J2.1, Q1.1 (G), R2.1
unnamed: J3.1, Q2.3 (C), R3.2
unnamed: J5.1, Q3.1 (G), R6.1
unnamed: J6.1, Q4.3 (C), R7.2
unnamed: Q1.2 (S), R3.1
unnamed: Q2.1 (B), R1.1, U1.3 (K)
unnamed: Q2.2 (E), R4.1, U1.1 (REF)
unnamed: Q3.2 (S), R7.1
unnamed: Q4.1 (B), R5.2, U2.3 (K)
unnamed: Q4.2 (E), R8.1, U2.1 (REF)
unnamed: R4.2, RV1.3
unnamed: R8.2, RV2.3

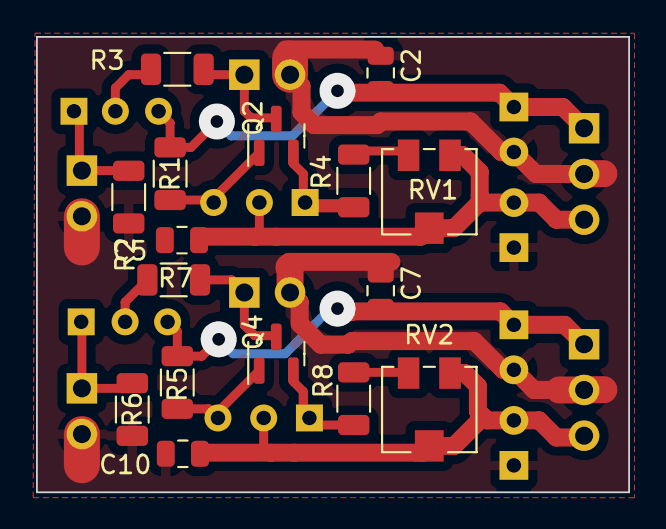
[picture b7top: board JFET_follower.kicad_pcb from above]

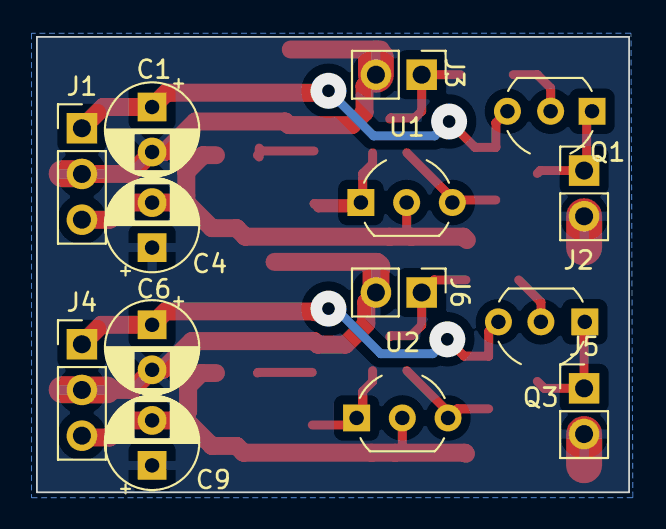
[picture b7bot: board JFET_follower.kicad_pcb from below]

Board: 2 copper layers, 32.9 x 25.3 mm, 30 parts (14 on the bottom side), 15 nets.
